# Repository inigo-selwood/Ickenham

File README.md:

# Ickenham

**Ickenham:** A tube station on the London Underground, but also a word which alliterates with "Instruction Set Architecture"

A RISC architecture designed to be compact, human-readable, and well-documented

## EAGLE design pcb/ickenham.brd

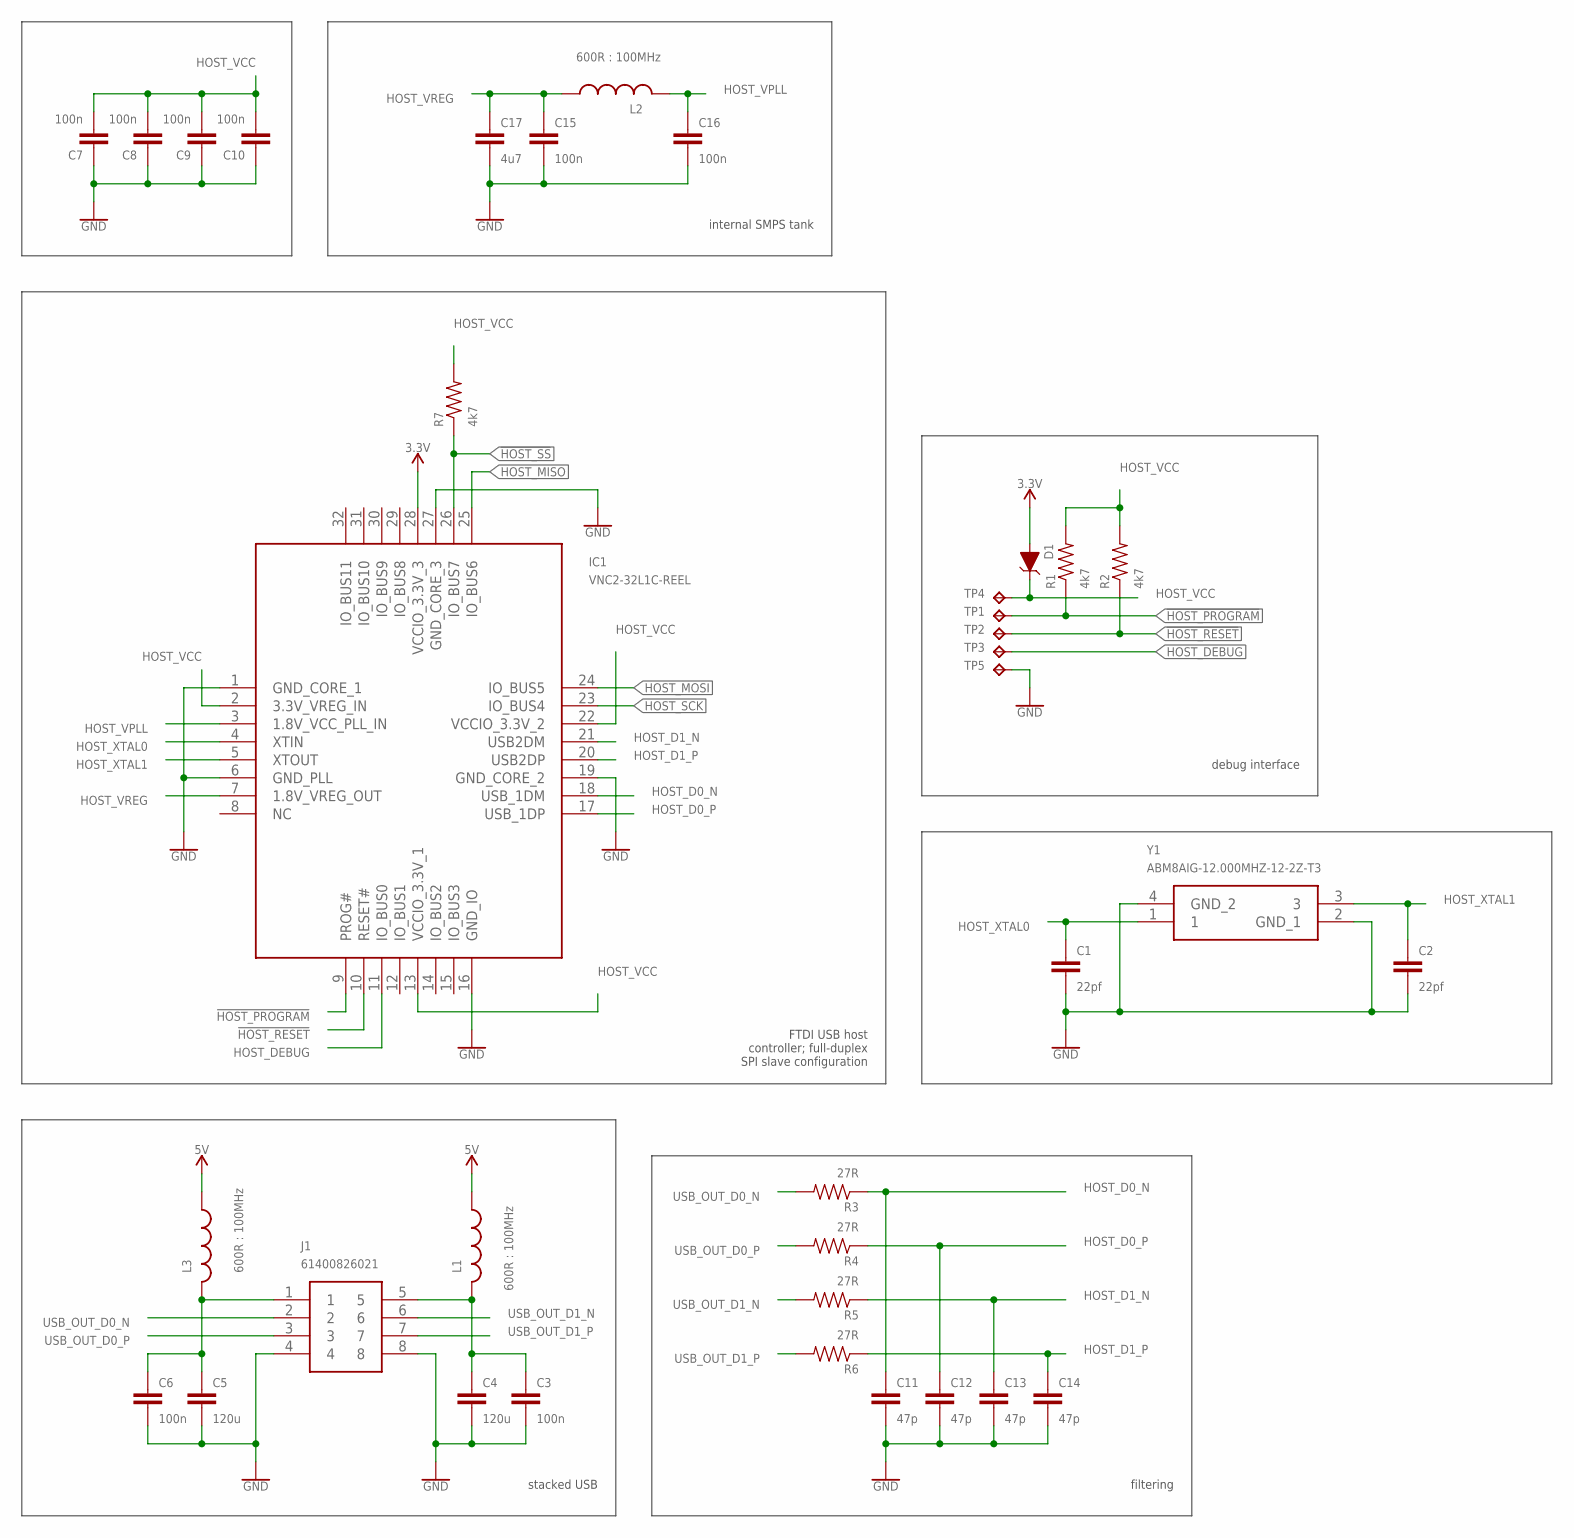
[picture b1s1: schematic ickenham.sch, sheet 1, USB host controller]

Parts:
C1, C2: 22pf; C0402
C3, C6, C15, C16: 100n; 0402-CAP
C4, C5: 120u; 0805
C7, C8, C9, C10: 100n; C0402
C11, C12, C13, C14: 47p; 0402-CAP
C17: 4u7; 0805
D1: 3.6V; SOD-323
IC1: VNC2-32L1C-REEL; QFP80P900X900X160-32N
J1: 61400826021; DUAL_USB_2.0_TYPE-A
L1, L2, L3: 600R : 100MHz; 0805
R1, R2, R7: 4k7; 0402-RES
R3, R4, R5, R6: 27R; 0805
TP1, TP2, TP3, TP5: TPTP10R; TP10R
TP4: TPTP10SQ; TP10SQ
Y1: ABM8AIG-12.000MHZ-12-2Z-T3; ABM8AIG25000MHZ122ZT3

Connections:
3.3V: D1.A, IC1.28 (VCCIO_3.3V_3); also elsewhere on the board
5V: L1.1, L3.1; also elsewhere on the board
!HOST_PROGRAM: IC1.9 (PROG#), R1.1, TP1.TP
!HOST_RESET: IC1.10 (RESET#), R2.1, TP2.TP
!HOST_SS: IC1.26 (IO_BUS7), R7.1; also elsewhere on the board
GND: C1.2, C2.2, C3.2, C4.2, C5.2, C6.2, C7.1, C8.1, C9.1, C10.1, C11.2, C12.2, C13.2, C14.2, C15.2, C16.2, C17.2, IC1.1 (GND_CORE_1), IC1.6 (GND_PLL), IC1.16 (GND_IO), IC1.19 (GND_CORE_2), IC1.27 (GND_CORE_3), J1.4, J1.8, TP5.TP, Y1.2 (GND_1), Y1.4 (GND_2); also elsewhere on the board
HOST_D0_N: C11.1, IC1.18 (USB_1DM), R3.1
HOST_D0_P: C12.1, IC1.17 (USB_1DP), R4.1
HOST_D1_N: C13.1, IC1.21 (USB2DM), R5.1
HOST_D1_P: C14.1, IC1.20 (USB2DP), R6.1
HOST_DEBUG: IC1.11 (IO_BUS0), TP3.TP
HOST_MISO: IC1.25 (IO_BUS6); also elsewhere on the board
HOST_MOSI: IC1.24 (IO_BUS5); also elsewhere on the board
HOST_SCK: IC1.23 (IO_BUS4); also elsewhere on the board
HOST_VCC: C7.2, C8.2, C9.2, C10.2, D1.C, IC1.2 (3.3V_VREG_IN), IC1.13 (VCCIO_3.3V_1), IC1.22 (VCCIO_3.3V_2), R1.2, R2.2, R7.2, TP4.TP
HOST_VPLL: C16.1, IC1.3 (1.8V_VCC_PLL_IN), L2.2
HOST_VREG: C15.1, C17.1, IC1.7 (1.8V_VREG_OUT), L2.1
HOST_XTAL0: C1.1, IC1.4 (XTIN), Y1.1
HOST_XTAL1: C2.1, IC1.5 (XTOUT), Y1.3
USB0_VCC: C5.1, C6.1, J1.1, L3.2
USB1_VCC: C3.1, C4.1, J1.5, L1.2
USB_OUT_D0_N: J1.2, R3.2
USB_OUT_D0_P: J1.3, R4.2
USB_OUT_D1_N: J1.6, R5.2
USB_OUT_D1_P: J1.7, R6.2

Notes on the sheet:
FTDI USB host controller; full-duplex SPI slave configuration
filtering
stacked USB
internal SMPS tank
debug interface

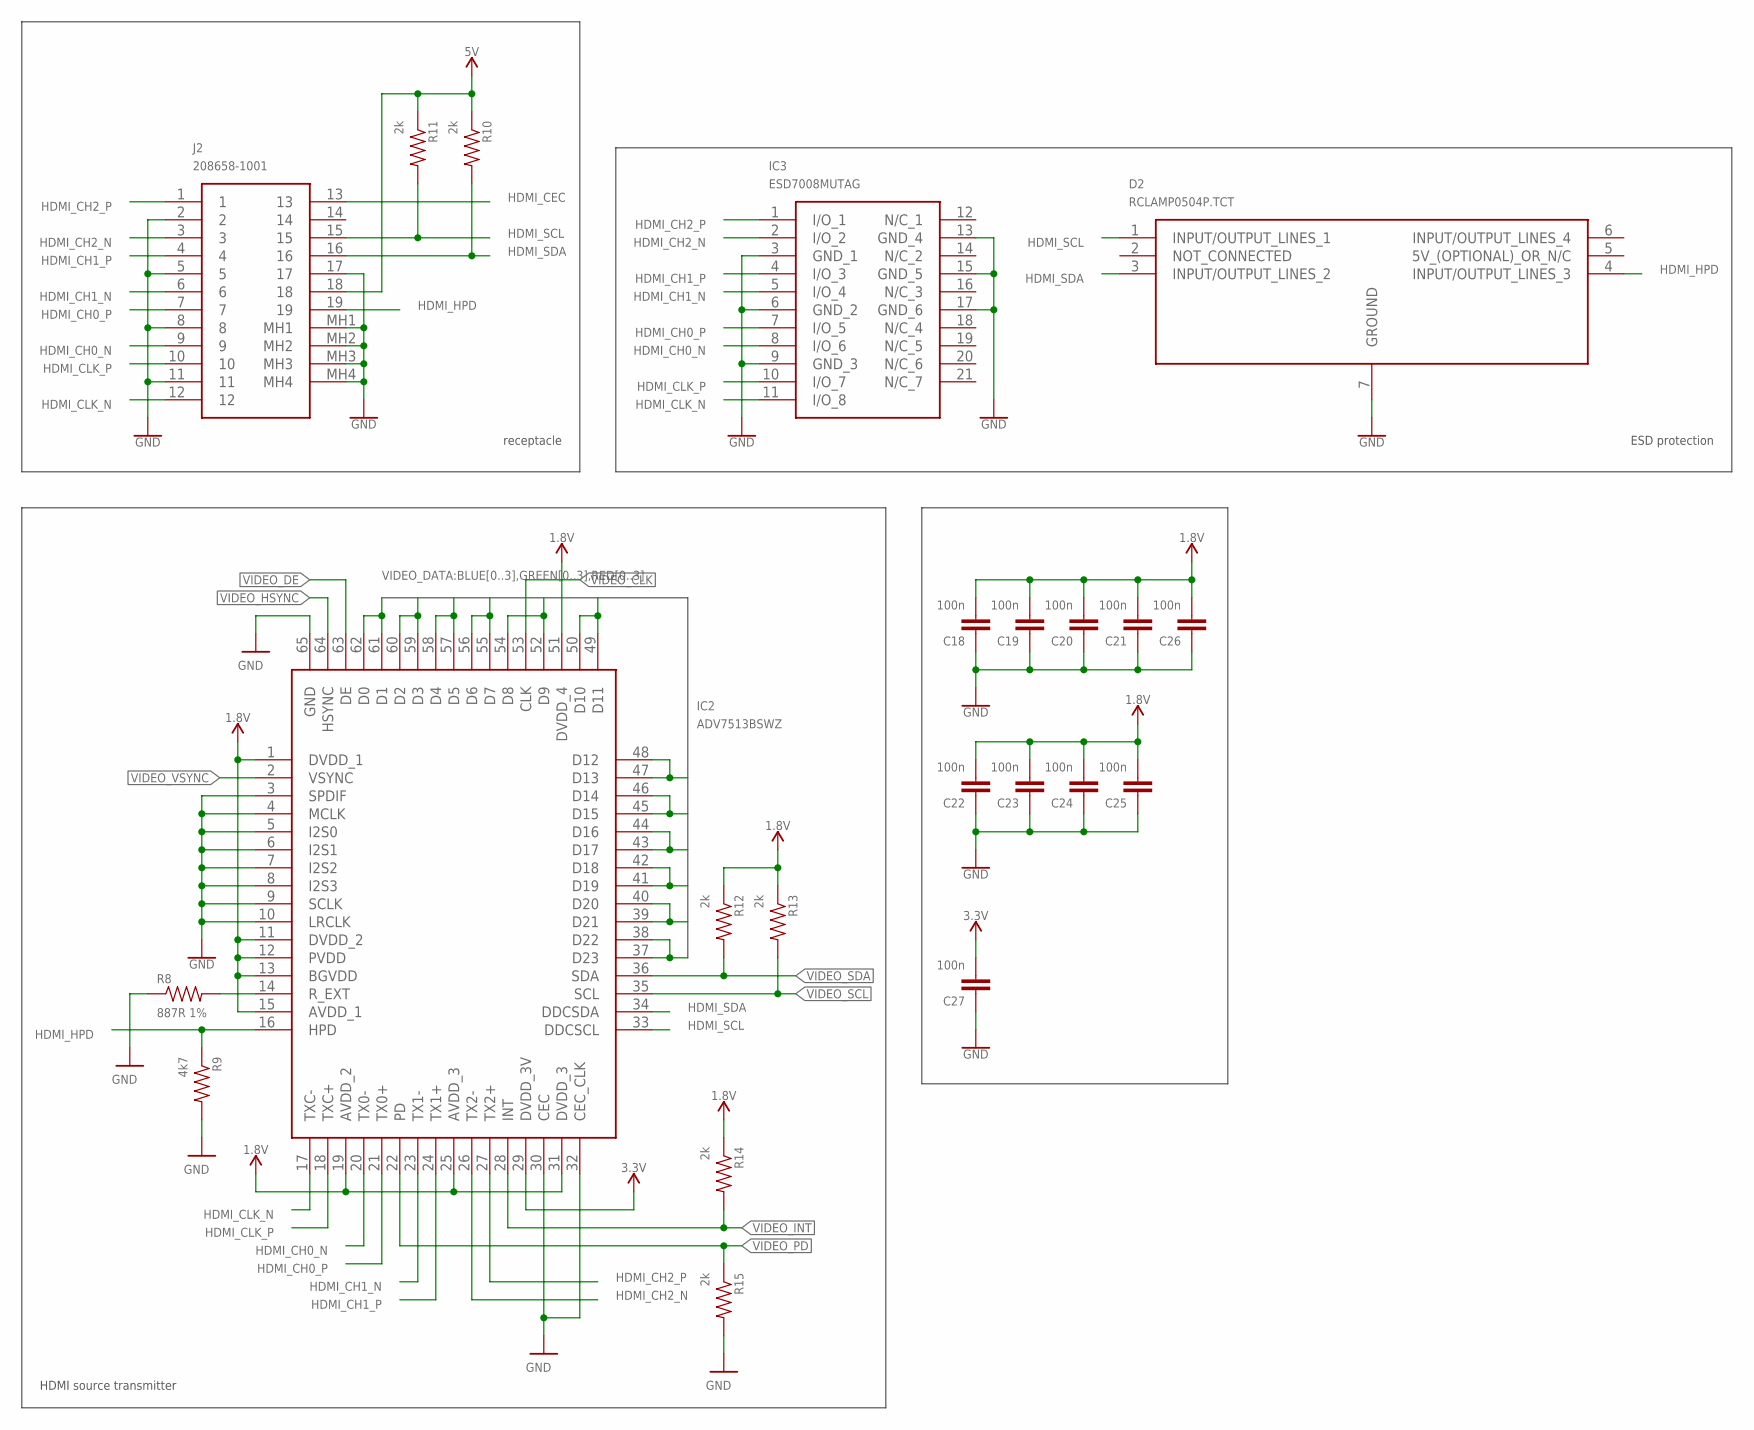
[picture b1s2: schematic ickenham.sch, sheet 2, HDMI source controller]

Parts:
C18, C19, C20, C21, C22, C23, C24, C25, C26, C27: 100n; C0402
D2: RCLAMP0504P.TCT; SON50P160X160X65-7N
IC2: ADV7513BSWZ; QFP50P1200X1200X160-65N
IC3: ESD7008MUTAG
J2: 208658-1001; 2086581001
R8: 887R 1%; 0805
R9: 4k7; 0402-RES
R10, R11, R12, R13, R14, R15: 2k; 0402-RES

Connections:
1.8V: C18.2, C19.2, C20.2, C21.2, C22.2, C23.2, C24.2, C25.2, C26.2, IC2.1 (DVDD_1), IC2.11 (DVDD_2), IC2.12 (PVDD), IC2.13 (BGVDD), IC2.15 (AVDD_1), IC2.19 (AVDD_2), IC2.25 (AVDD_3), IC2.31 (DVDD_3), IC2.51 (DVDD_4), R12.1, R13.1, R14.1
3.3V: C27.2, IC2.29 (DVDD_3V); also elsewhere on the board
5V: J2.18, R10.1, R11.1; also elsewhere on the board
GND: C18.1, C19.1, C20.1, C21.1, C22.1, C23.1, C24.1, C25.1, C26.1, C27.1, D2.7 (GROUND), IC2.3 (SPDIF), IC2.4 (MCLK), IC2.5 (I2S0), IC2.6 (I2S1), IC2.7 (I2S2), IC2.8 (I2S3), IC2.9 (SCLK), IC2.10 (LRCLK), IC2.30 (CEC), IC2.32 (CEC_CLK), IC2.65 (GND), IC3.3 (GND_1), IC3.6 (GND_2), IC3.9 (GND_3), IC3.13 (GND_4), IC3.15 (GND_5), IC3.17 (GND_6), J2.2, J2.5, J2.8, J2.11, J2.17, J2.MH1, J2.MH2, J2.MH3, J2.MH4, R8.1, R9.2, R15.2; also elsewhere on the board
HDMI_CEC: J2.13
HDMI_CH0_N: IC2.20 (TX0-), IC3.8 (I/O_6), J2.9
HDMI_CH0_P: IC2.21 (TX0+), IC3.7 (I/O_5), J2.7
HDMI_CH1_N: IC2.23 (TX1-), IC3.5 (I/O_4), J2.6
HDMI_CH1_P: IC2.24 (TX1+), IC3.4 (I/O_3), J2.4
HDMI_CH2_N: IC2.26 (TX2-), IC3.2 (I/O_2), J2.3
HDMI_CH2_P: IC2.27 (TX2+), IC3.1 (I/O_1), J2.1
HDMI_CLK_N: IC2.17 (TXC-), IC3.11 (I/O_8), J2.12
HDMI_CLK_P: IC2.18 (TXC+), IC3.10 (I/O_7), J2.10
HDMI_HPD: D2.4 (INPUT/OUTPUT_LINES_3), IC2.16 (HPD), J2.19, R9.1
HDMI_SCL: D2.1 (INPUT/OUTPUT_LINES_1), IC2.33 (DDCSCL), J2.15, R11.2
HDMI_SDA: D2.3 (INPUT/OUTPUT_LINES_2), IC2.34 (DDCSDA), J2.16, R10.2
unnamed: IC2.14 (R_EXT), R8.2
VIDEO_BLUE0: IC2.61 (D1), IC2.62 (D0); also elsewhere on the board
VIDEO_BLUE1: IC2.59 (D3), IC2.60 (D2); also elsewhere on the board
VIDEO_BLUE2: IC2.57 (D5), IC2.58 (D4); also elsewhere on the board
VIDEO_BLUE3: IC2.55 (D7), IC2.56 (D6); also elsewhere on the board
VIDEO_CLK: IC2.53 (CLK); also elsewhere on the board
VIDEO_DE: IC2.63 (DE); also elsewhere on the board
VIDEO_GREEN0: IC2.52 (D9), IC2.54 (D8); also elsewhere on the board
VIDEO_GREEN1: IC2.49 (D11), IC2.50 (D10); also elsewhere on the board
VIDEO_GREEN2: IC2.47 (D13), IC2.48 (D12); also elsewhere on the board
VIDEO_GREEN3: IC2.45 (D15), IC2.46 (D14); also elsewhere on the board
VIDEO_HSYNC: IC2.64 (HSYNC); also elsewhere on the board
VIDEO_INT: IC2.28 (INT), R14.2
VIDEO_PD: IC2.22 (PD), R15.1
VIDEO_RED0: IC2.43 (D17), IC2.44 (D16); also elsewhere on the board
VIDEO_RED1: IC2.41 (D19), IC2.42 (D18); also elsewhere on the board
VIDEO_RED2: IC2.39 (D21), IC2.40 (D20); also elsewhere on the board
VIDEO_RED3: IC2.37 (D23), IC2.38 (D22); also elsewhere on the board
VIDEO_SCL: IC2.35 (SCL), R13.2; also elsewhere on the board
VIDEO_SDA: IC2.36 (SDA), R12.2; also elsewhere on the board
VIDEO_VSYNC: IC2.2 (VSYNC); also elsewhere on the board

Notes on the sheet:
HDMI source transmitter
ESD protection
receptacle

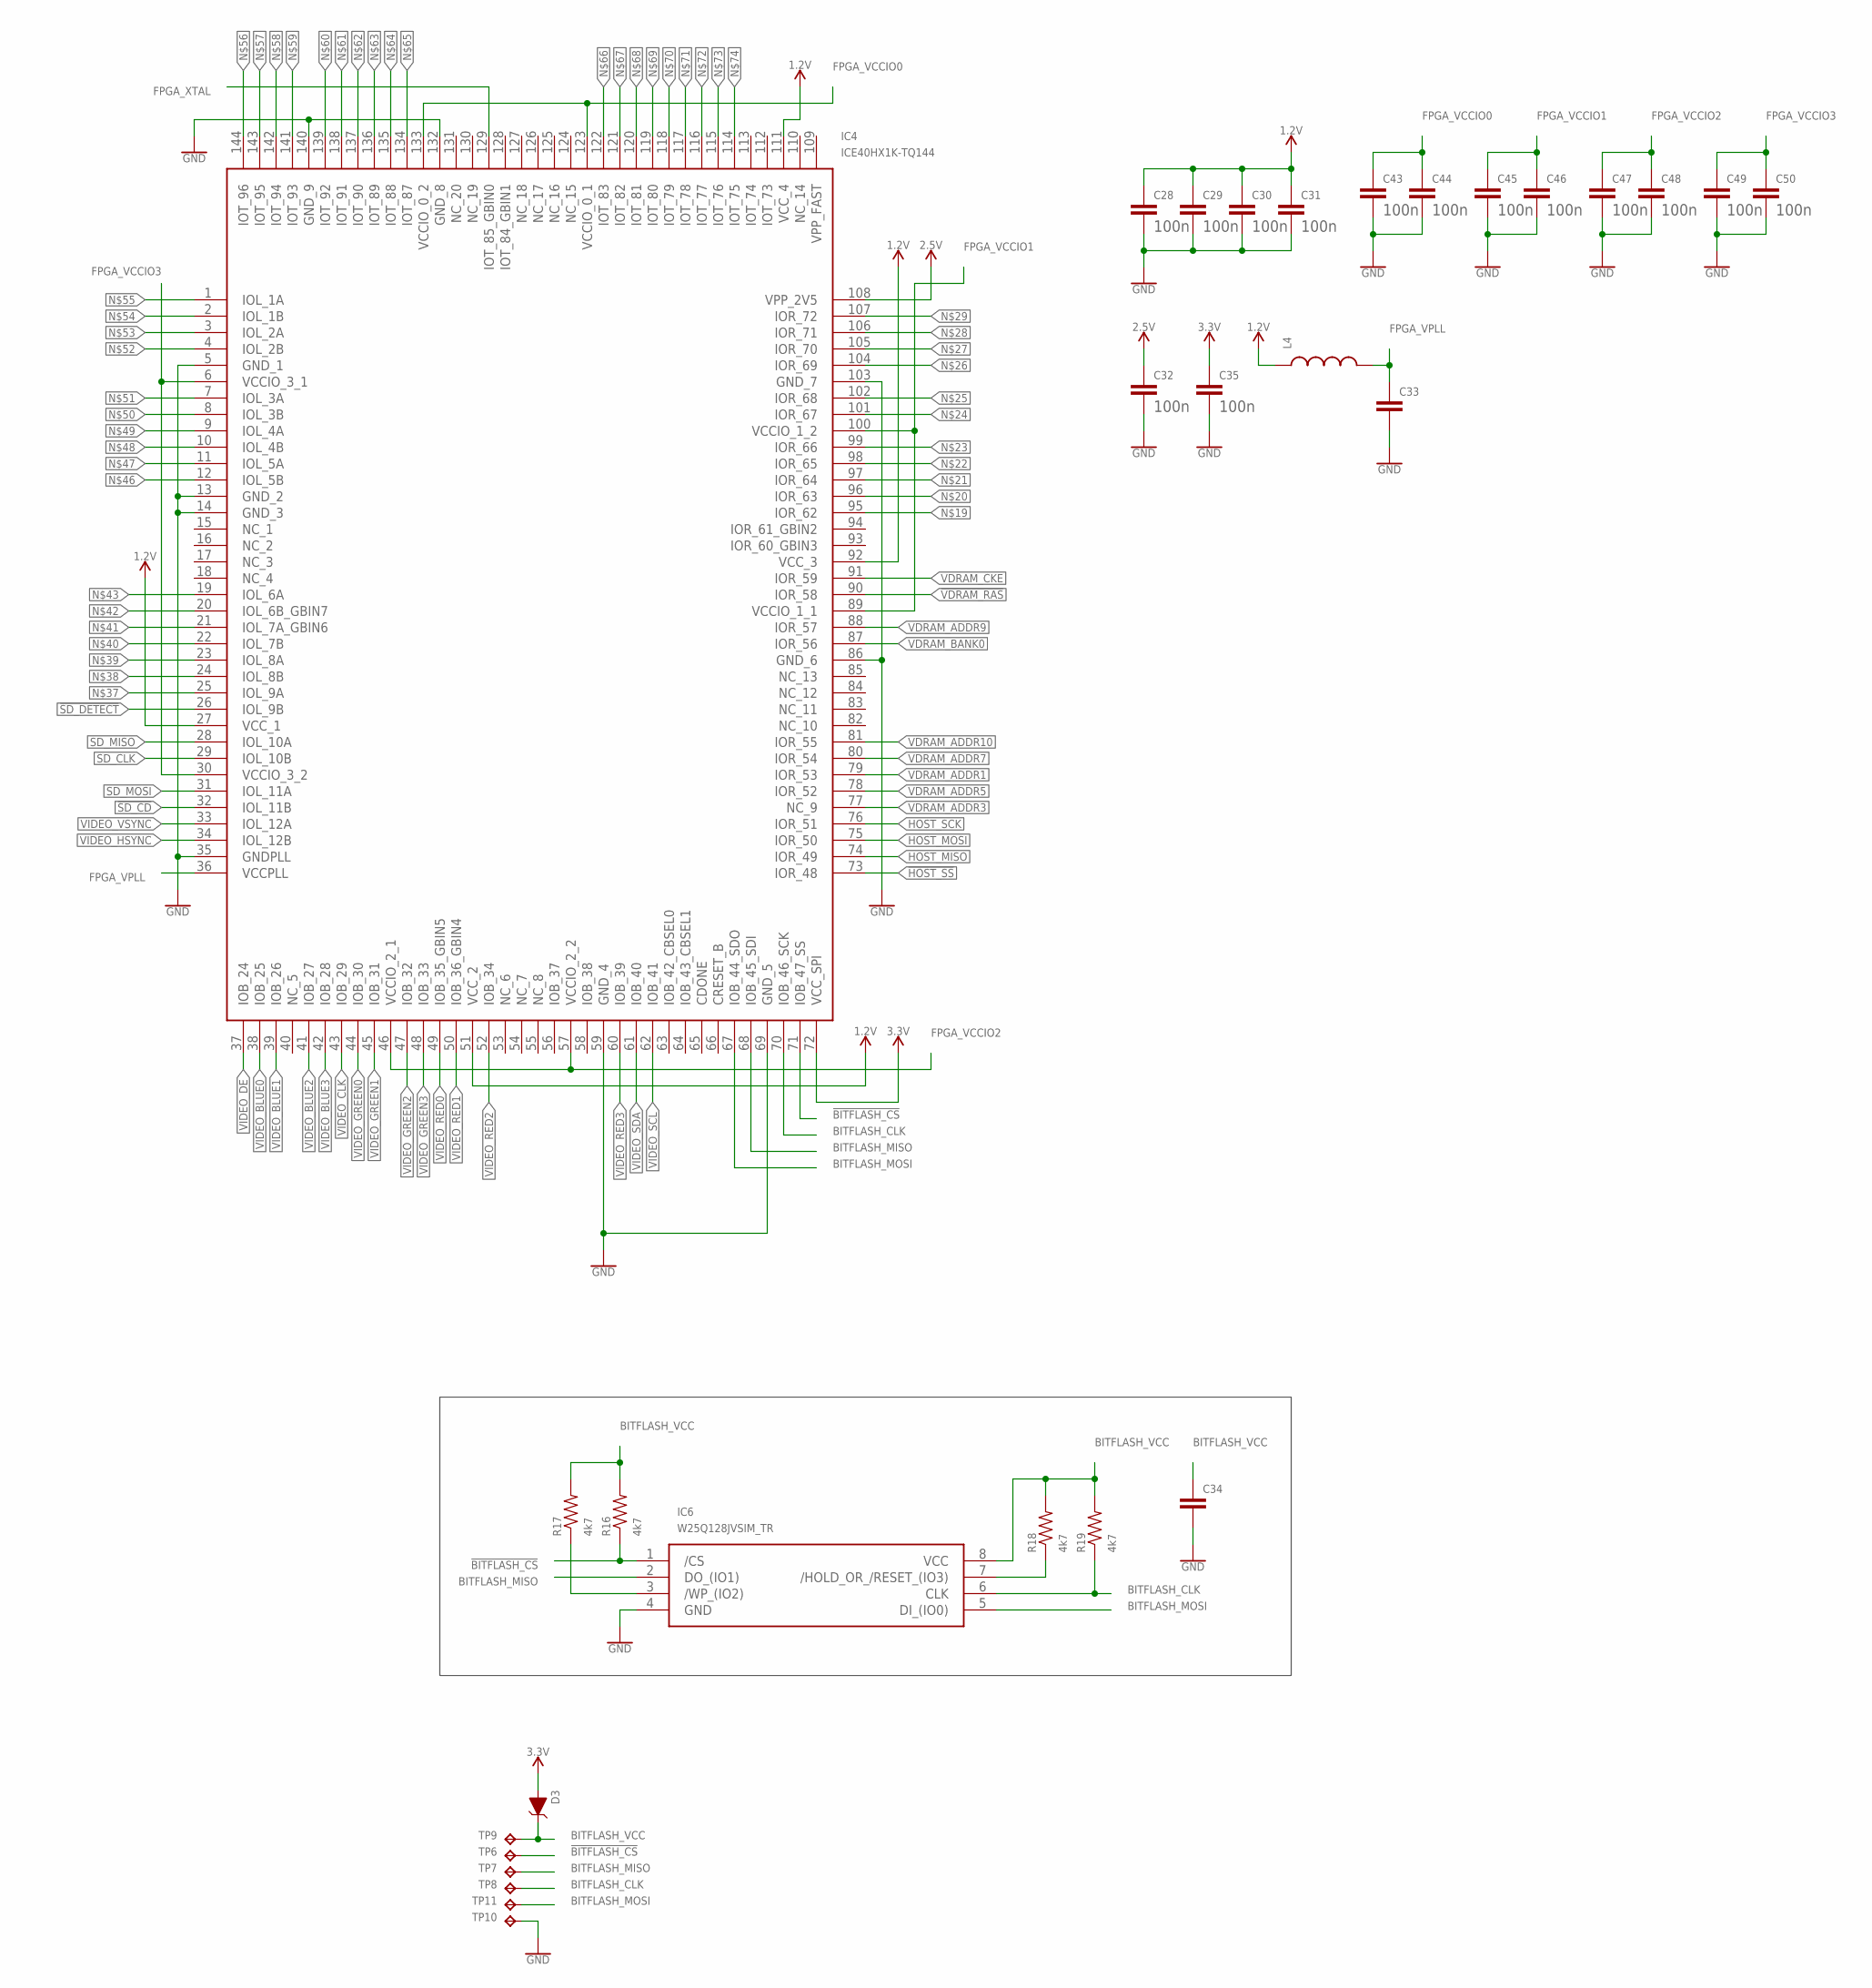
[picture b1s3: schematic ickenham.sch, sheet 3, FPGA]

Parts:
C28, C29, C30, C31, C32, C35, C43, C44, C45, C46, C47, C48, C49, C50: 100n; 0402-CAP
C33, C34: CAP0402-CAP; 0402-CAP
D3: 3.6V; SOD-323
IC4: ICE40HX1K-TQ144; QFP50P2200X2200X160-144N
IC6: W25Q128JVSIM_TR; SOIC127P790X216-8N
L4: INDUCTOR0805; 0805
R16, R17, R18, R19: 4k7; 0402-RES
TP6, TP7, TP8, TP10, TP11: TPTP10R; TP10R
TP9: TPTP10SQ; TP10SQ

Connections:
1.2V: C28.1, C29.1, C30.1, C31.1, IC4.27 (VCC_1), IC4.51 (VCC_2), IC4.92 (VCC_3), IC4.111 (VCC_4), L4.1
2.5V: C32.1, IC4.108 (VPP_2V5)
3.3V: C35.1, D3.A, IC4.72 (VCC_SPI); also elsewhere on the board
!BITFLASH_CS: IC4.71 (IOB_47_SS), IC6.1 (/CS), R16.1, TP6.TP
!HOST_SS: IC4.73 (IOR_48); also elsewhere on the board
!SD_CD: IC4.32 (IOL_11B); also elsewhere on the board
!SD_DETECT: IC4.26 (IOL_9B); also elsewhere on the board
!VDRAM_RAS: IC4.90 (IOR_58); also elsewhere on the board
BITFLASH_CLK: IC4.70 (IOB_46_SCK), IC6.6 (CLK), R19.1, TP8.TP
BITFLASH_MISO: IC4.68 (IOB_45_SDI), IC6.2 (DO_(IO1)), TP7.TP
BITFLASH_MOSI: IC4.67 (IOB_44_SDO), IC6.5 (DI_(IO0)), TP11.TP
BITFLASH_VCC: C34.1, D3.C, IC6.8 (VCC), R16.2, R17.2, R18.2, R19.2, TP9.TP
FPGA_VCCIO0: C43.1, C44.1, IC4.123 (VCCIO_0_1), IC4.133 (VCCIO_0_2)
FPGA_VCCIO1: C45.1, C46.1, IC4.89 (VCCIO_1_1), IC4.100 (VCCIO_1_2)
FPGA_VCCIO2: C47.1, C48.1, IC4.46 (VCCIO_2_1), IC4.57 (VCCIO_2_2)
FPGA_VCCIO3: C49.1, C50.1, IC4.6 (VCCIO_3_1), IC4.30 (VCCIO_3_2)
FPGA_VPLL: C33.1, IC4.36 (VCCPLL), L4.2
FPGA_XTAL: IC4.129 (IOT_85_GBIN0)
GND: C28.2, C29.2, C30.2, C31.2, C32.2, C33.2, C34.2, C35.2, C43.2, C44.2, C45.2, C46.2, C47.2, C48.2, C49.2, C50.2, IC4.5 (GND_1), IC4.13 (GND_2), IC4.14 (GND_3), IC4.35 (GNDPLL), IC4.59 (GND_4), IC4.69 (GND_5), IC4.86 (GND_6), IC4.103 (GND_7), IC4.132 (GND_8), IC4.140 (GND_9), IC6.4 (GND), TP10.TP; also elsewhere on the board
HOST_MISO: IC4.74 (IOR_49); also elsewhere on the board
HOST_MOSI: IC4.75 (IOR_50); also elsewhere on the board
HOST_SCK: IC4.76 (IOR_51); also elsewhere on the board
unnamed: IC6.3 (/WP_(IO2)), R17.1
unnamed: IC6.7 (/HOLD_OR_/RESET_(IO3)), R18.1
SD_CLK: IC4.29 (IOL_10B); also elsewhere on the board
SD_MISO: IC4.28 (IOL_10A); also elsewhere on the board
SD_MOSI: IC4.31 (IOL_11A); also elsewhere on the board
VDRAM_ADDR1: IC4.79 (IOR_53); also elsewhere on the board
VDRAM_ADDR3: IC4.77 (NC_9); also elsewhere on the board
VDRAM_ADDR5: IC4.78 (IOR_52); also elsewhere on the board
VDRAM_ADDR7: IC4.80 (IOR_54); also elsewhere on the board
VDRAM_ADDR9: IC4.88 (IOR_57); also elsewhere on the board
VDRAM_ADDR10: IC4.81 (IOR_55); also elsewhere on the board
VDRAM_BANK0: IC4.87 (IOR_56); also elsewhere on the board
VDRAM_CKE: IC4.91 (IOR_59); also elsewhere on the board
VIDEO_BLUE0: IC4.38 (IOB_25); also elsewhere on the board
VIDEO_BLUE1: IC4.39 (IOB_26); also elsewhere on the board
VIDEO_BLUE2: IC4.41 (IOB_27); also elsewhere on the board
VIDEO_BLUE3: IC4.42 (IOB_28); also elsewhere on the board
VIDEO_CLK: IC4.43 (IOB_29); also elsewhere on the board
VIDEO_DE: IC4.37 (IOB_24); also elsewhere on the board
VIDEO_GREEN0: IC4.44 (IOB_30); also elsewhere on the board
VIDEO_GREEN1: IC4.45 (IOB_31); also elsewhere on the board
VIDEO_GREEN2: IC4.47 (IOB_32); also elsewhere on the board
VIDEO_GREEN3: IC4.48 (IOB_33); also elsewhere on the board
VIDEO_HSYNC: IC4.34 (IOL_12B); also elsewhere on the board
VIDEO_RED0: IC4.49 (IOB_35_GBIN5); also elsewhere on the board
VIDEO_RED1: IC4.50 (IOB_36_GBIN4); also elsewhere on the board
VIDEO_RED2: IC4.52 (IOB_34); also elsewhere on the board
VIDEO_RED3: IC4.60 (IOB_39); also elsewhere on the board
VIDEO_SCL: IC4.62 (IOB_41); also elsewhere on the board
VIDEO_SDA: IC4.61 (IOB_40); also elsewhere on the board
VIDEO_VSYNC: IC4.33 (IOL_12A); also elsewhere on the board

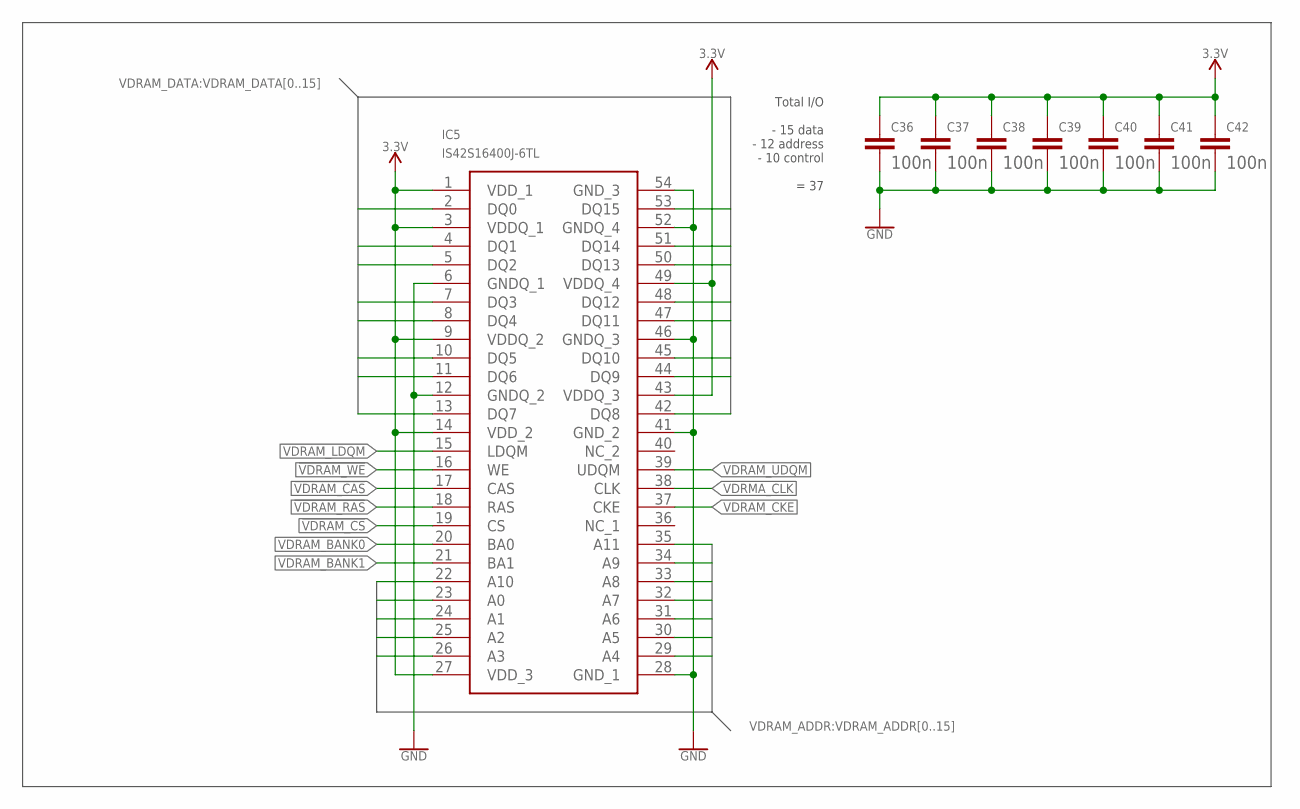
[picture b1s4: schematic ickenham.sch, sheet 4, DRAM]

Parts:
C36, C37, C38, C39, C40, C41, C42: 100n; 0402-CAP
IC5: IS42S16400J-6TL; SOP80P1176X120-54N

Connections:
3.3V: C36.1, C37.1, C38.1, C39.1, C40.1, C41.1, C42.1, IC5.1 (VDD_1), IC5.3 (VDDQ_1), IC5.9 (VDDQ_2), IC5.14 (VDD_2), IC5.27 (VDD_3), IC5.43 (VDDQ_3), IC5.49 (VDDQ_4); also elsewhere on the board
!VDRAM_CAS: IC5.17 (CAS)
!VDRAM_CS: IC5.19 (CS)
!VDRAM_RAS: IC5.18 (RAS); also elsewhere on the board
!VDRAM_WE: IC5.16 (WE)
GND: C36.2, C37.2, C38.2, C39.2, C40.2, C41.2, C42.2, IC5.6 (GNDQ_1), IC5.12 (GNDQ_2), IC5.28 (GND_1), IC5.41 (GND_2), IC5.46 (GNDQ_3), IC5.52 (GNDQ_4), IC5.54 (GND_3); also elsewhere on the board
VDRAM_ADDR0: IC5.23 (A0)
VDRAM_ADDR1: IC5.24 (A1); also elsewhere on the board
VDRAM_ADDR2: IC5.25 (A2)
VDRAM_ADDR3: IC5.26 (A3); also elsewhere on the board
VDRAM_ADDR4: IC5.29 (A4)
VDRAM_ADDR5: IC5.30 (A5); also elsewhere on the board
VDRAM_ADDR6: IC5.31 (A6)
VDRAM_ADDR7: IC5.32 (A7); also elsewhere on the board
VDRAM_ADDR8: IC5.33 (A8)
VDRAM_ADDR9: IC5.34 (A9); also elsewhere on the board
VDRAM_ADDR10: IC5.22 (A10); also elsewhere on the board
VDRAM_ADDR11: IC5.35 (A11)
VDRAM_BANK0: IC5.20 (BA0); also elsewhere on the board
VDRAM_BANK1: IC5.21 (BA1)
VDRAM_CKE: IC5.37 (CKE); also elsewhere on the board
VDRAM_DATA0: IC5.2 (DQ0)
VDRAM_DATA1: IC5.4 (DQ1)
VDRAM_DATA2: IC5.5 (DQ2)
VDRAM_DATA3: IC5.7 (DQ3)
VDRAM_DATA4: IC5.8 (DQ4)
VDRAM_DATA5: IC5.10 (DQ5)
VDRAM_DATA6: IC5.11 (DQ6)
VDRAM_DATA7: IC5.13 (DQ7)
VDRAM_DATA8: IC5.42 (DQ8)
VDRAM_DATA9: IC5.44 (DQ9)
VDRAM_DATA10: IC5.45 (DQ10)
VDRAM_DATA11: IC5.47 (DQ11)
VDRAM_DATA12: IC5.48 (DQ12)
VDRAM_DATA13: IC5.50 (DQ13)
VDRAM_DATA14: IC5.51 (DQ14)
VDRAM_DATA15: IC5.53 (DQ15)
VDRAM_LDQM: IC5.15 (LDQM)
VDRAM_UDQM: IC5.39 (UDQM)
VDRMA_CLK: IC5.38 (CLK)

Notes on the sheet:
Total I/O - 15 data - 12 address - 10 control = 37

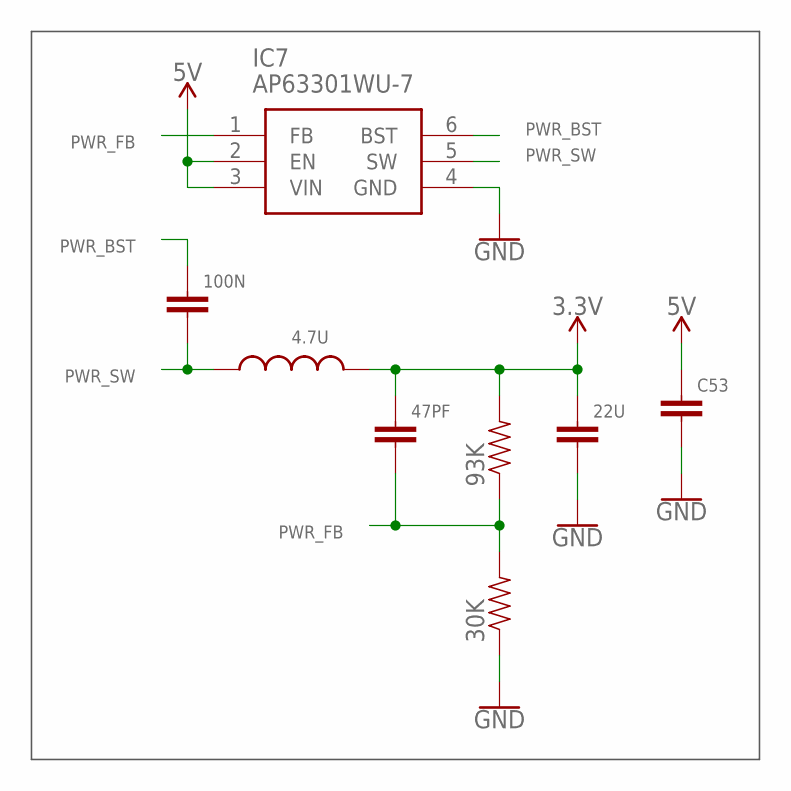
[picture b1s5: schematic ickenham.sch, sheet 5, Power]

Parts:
4.7U: INDUCTOR1210; 1210
22U: CAP1206; 1206
30K, 93K: RESISTOR0402-RES; 0402-RES
47PF, 100N: CAP0402-CAP; 0402-CAP
C53: CAP1206; 1206
IC7: AP63301WU-7; SOT95P280X100-6N

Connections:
3.3V: 4.7U.2, 22U.1, 47PF.1, 93K.2; also elsewhere on the board
5V: C53.1, IC7.2 (EN), IC7.3 (VIN); also elsewhere on the board
GND: 22U.2, 30K.1, C53.2, IC7.4 (GND); also elsewhere on the board
PWR_BST: 100N.1, IC7.6 (BST)
PWR_FB: 30K.2, 47PF.2, 93K.1, IC7.1 (FB)
PWR_SW: 4.7U.1, 100N.2, IC7.5 (SW)

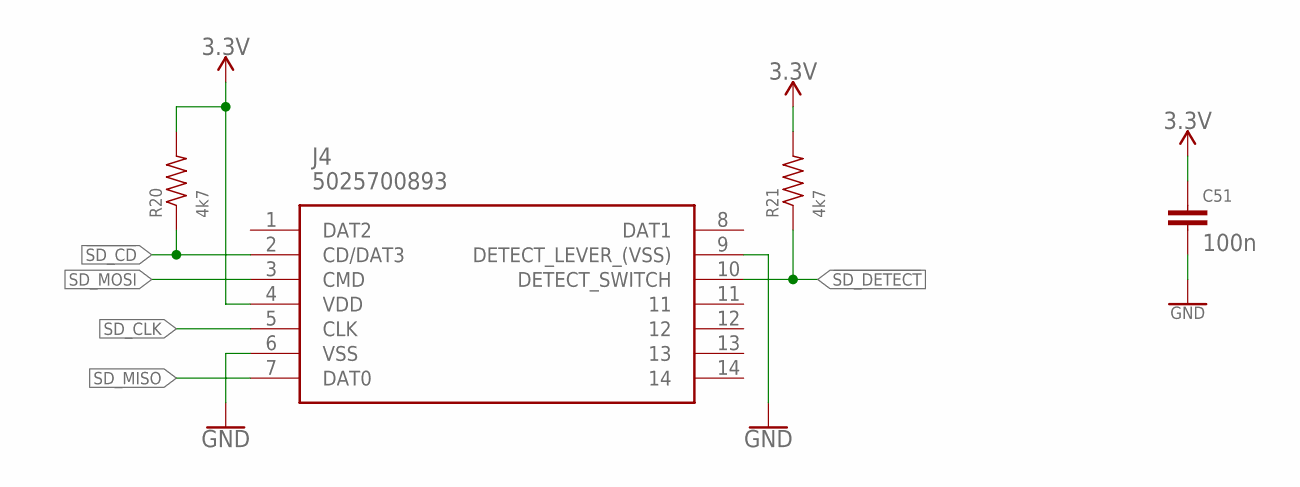
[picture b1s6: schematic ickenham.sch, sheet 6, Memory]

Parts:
C51: 100n; 0402-CAP
J4: 5025700893
R20, R21: 4k7; 0402-RES

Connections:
3.3V: C51.1, J4.4 (VDD), R20.2, R21.2; also elsewhere on the board
!SD_CD: J4.2 (CD/DAT3), R20.1; also elsewhere on the board
!SD_DETECT: J4.10 (DETECT_SWITCH), R21.1; also elsewhere on the board
GND: C51.2, J4.6 (VSS), J4.9 (DETECT_LEVER_(VSS)); also elsewhere on the board
SD_CLK: J4.5 (CLK); also elsewhere on the board
SD_MISO: J4.7 (DAT0); also elsewhere on the board
SD_MOSI: J4.3 (CMD); also elsewhere on the board

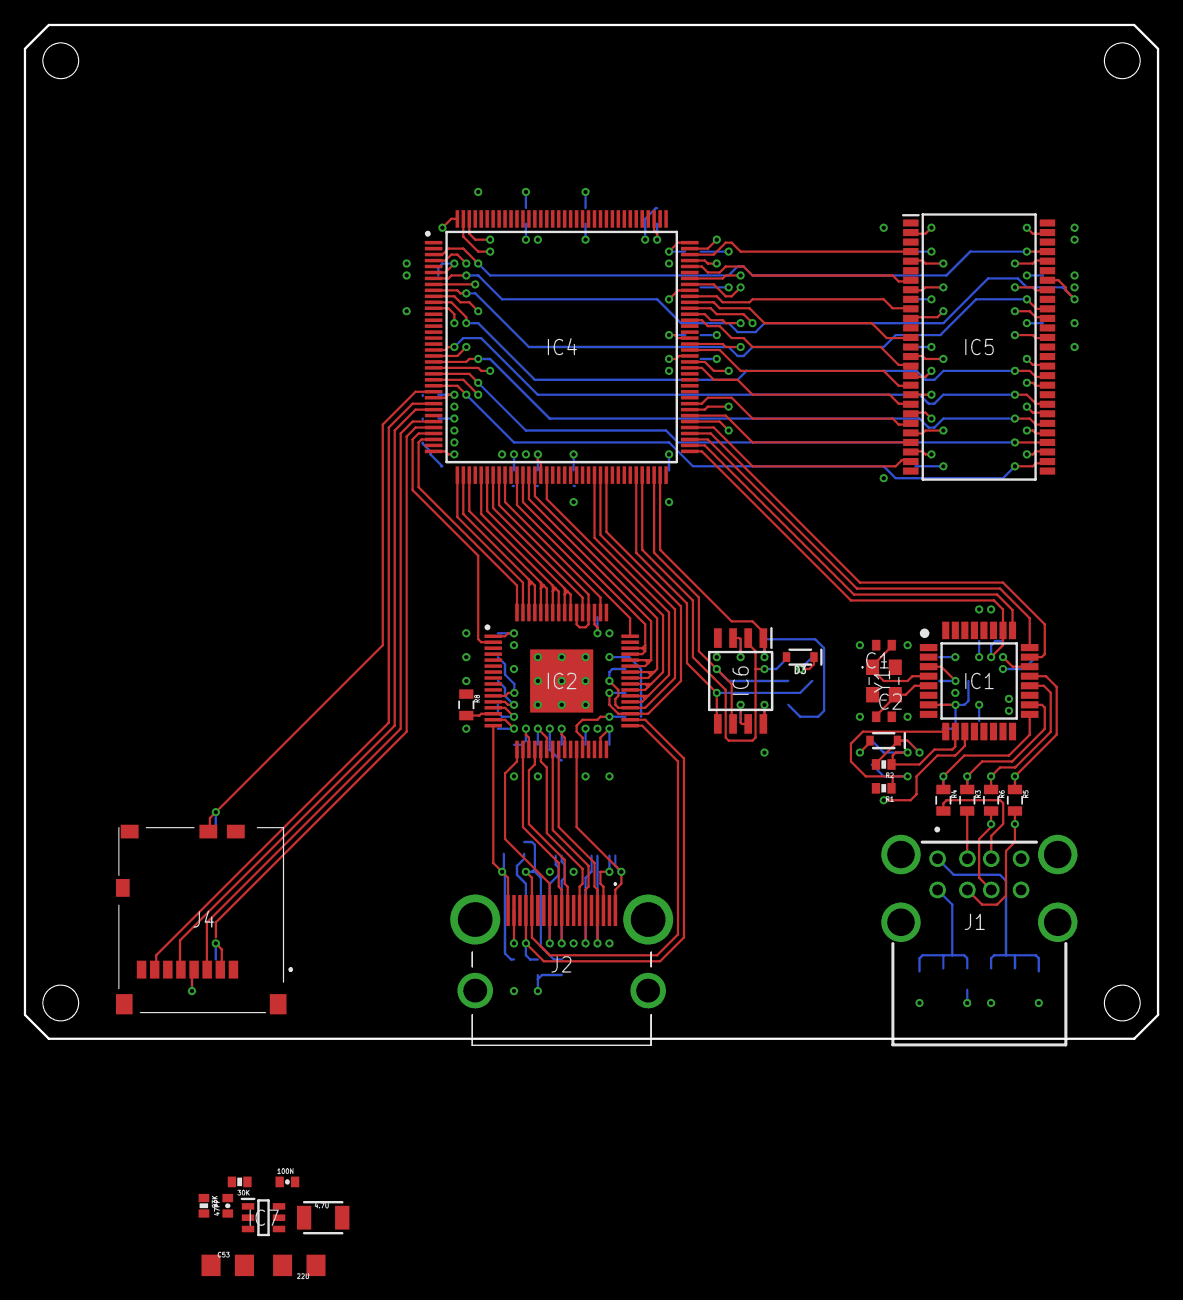
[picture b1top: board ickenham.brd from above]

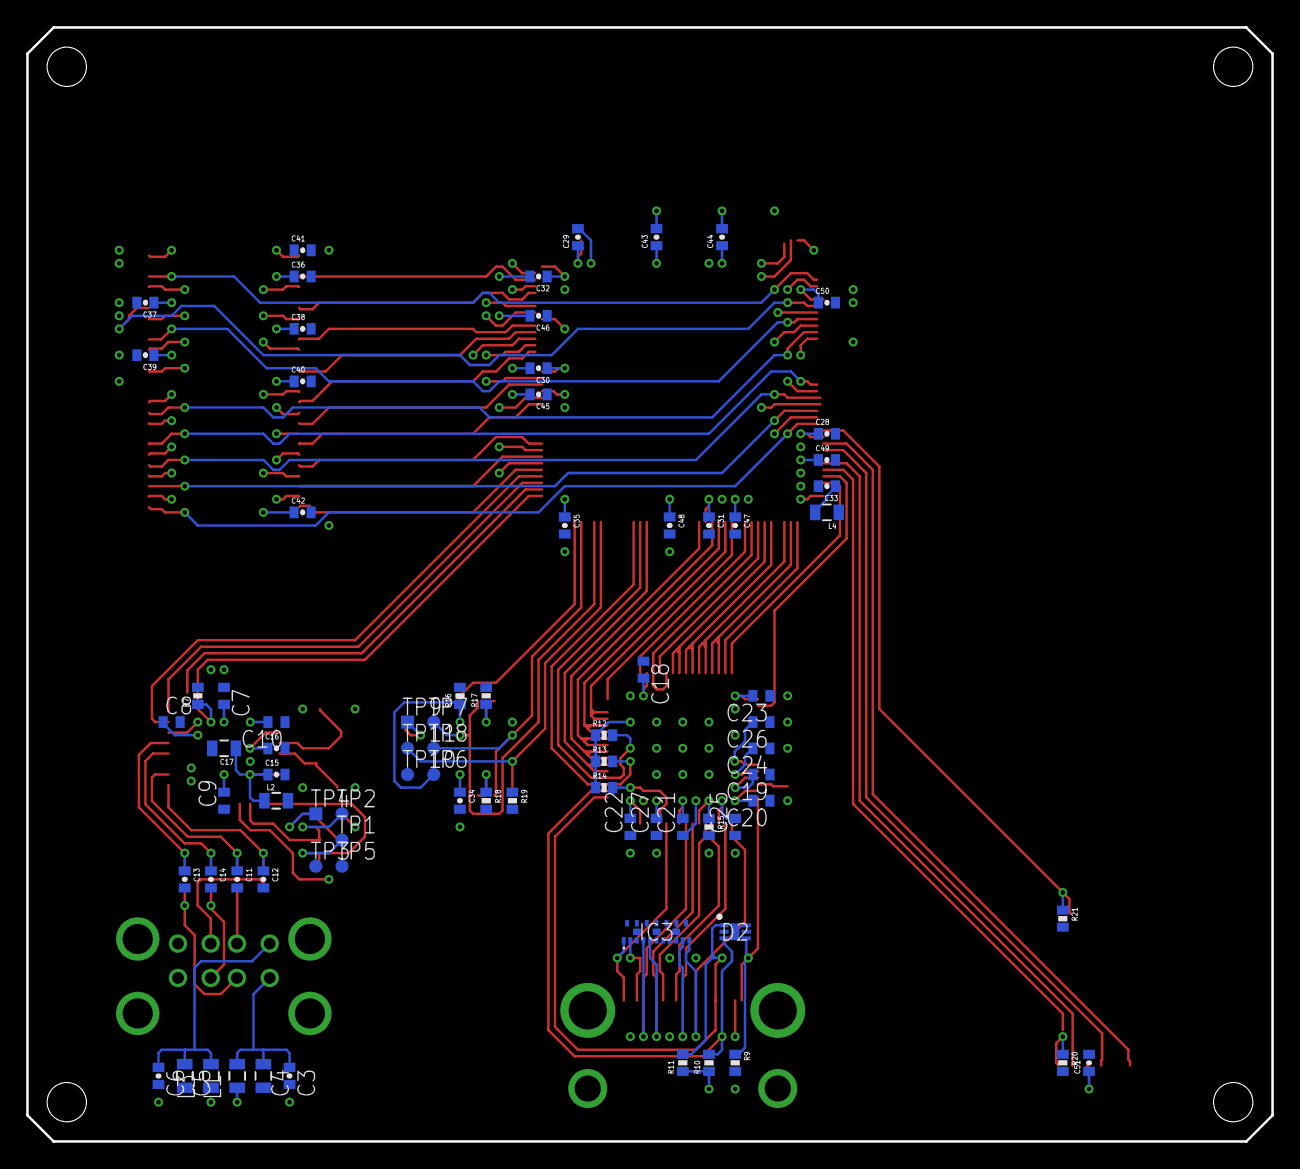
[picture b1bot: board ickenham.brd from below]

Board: 6 copper layers, 95.0 x 85.0 mm, 108 parts (80 on the bottom side), 89 nets.

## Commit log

2022-04-16 Fresh start
2022-04-16 Added arithmetic blocks
2022-04-21 Added documentation
2022-04-21 Added integer arithmetic blocks
2022-04-21 Added leading zero counter
2022-04-22 Added fetch stage
2022-11-14 removed quartus backup files
2022-11-14 added instruction set specification
2022-12-08 moved hdl to subfolder
2022-12-08 added libraries
2022-12-08 added schematic, diagram

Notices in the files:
parts and their libraries:
discrete: Licensing: Creative Commons ShareAlike 4.0 International - https://creativecommons.org/licenses/by-sa/4.0
